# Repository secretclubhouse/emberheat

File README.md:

# EmberHeat

A Matter-enabled multi-zone thermostat system for hydronic heating, written in Rust for ESP32-C6. Controls heating zones via HomeKit, Google Home, and other Matter-compatible controllers.

## Architecture

**Cargo workspace** with three active crates:

| Crate | Purpose | Platform |
|-------|---------|----------|
| `emberheat-core` | Core control logic, traits, types | `no_std` compatible |
| `emberheat-matter` | Matter protocol types and cluster definitions | `no_std` compatible |
| `emberheat-esp32` | ESP32-C6 firmware (active) | ESP32-C6 bare-metal |
| `emberheat-linux` | Raspberry Pi implementation (preserved) | Linux |

### Core Library (`emberheat-core`)

Platform-agnostic library containing:
- **Temperature types** with Celsius/Fahrenheit conversion
- **Hysteresis control algorithm** (prevents relay chatter with ±0.5°C dead band)
- **Trait definitions** for sensors, GPIO, and state persistence
- **Sensor validation** (0°C - 37°C range)

### Matter Integration (`emberheat-matter`)

Smart home protocol support via [rs-matter](https://github.com/project-chip/rs-matter):
- **Thermostat Cluster** (0x0201) with heating and cooling support
- **Atomic state management** for cross-task zone state access
- **Zone-aware state** with target temperatures and system modes
- **Lock-free design** using portable-atomic for real-time safety
- **Dirty flag tracking** for efficient flash persistence

### ESP32 Implementation (`emberheat-esp32`)

Active firmware for ESP32-C6:
- **Embassy async runtime** for cooperative multitasking
- **Matter stack** with BLE + WiFi commissioning (single-radio and dual-radio modes)
- **Flash persistence** with wear-leveling via sequential-storage
- **Factory reset** via GPIO button (hold 5 seconds)
- **1-Wire temperature sensors** via RMT peripheral
- **BME280 I2C sensor** support
- **Relay control** via GPIO
- **WiFi connectivity** provisioned through Matter commissioning
- **MQTT logging** for monitoring
- **Matter bridge** connecting protocol state to control loops

### Linux Implementation (`emberheat-linux`)

Preserved but not actively developed. Uses:
- `rppal` for Raspberry Pi GPIO control
- 1-Wire via sysfs (`/sys/bus/w1/devices/`)
- HTTP fallback sensors via `reqwest`
- Redis for state persistence
- Prometheus for metrics export

## Quick Start (ESP32-C6)

### Prerequisites

```bash
# Install Rust (if needed)
curl --proto '=https' --tlsv1.2 -sSf https://sh.rustup.rs | sh

# Add ESP32 target
rustup target add riscv32imac-unknown-none-elf

# Install espflash
cargo install espflash
```

### Build and Flash

```bash
# Build with Matter support (single-radio: C6 WiFi + BLE time-shared)
make build-matter

# Build with dual-radio (C6 WiFi + H2 BLE over UART HCI)
make build-matter-dual-radio

# Flash Matter firmware and monitor serial output
make flash-monitor-matter

# Run tests (emberheat-core + emberheat-matter)
make test
```

### Matter Commissioning

After flashing, the device enters commissioning mode. Use the Apple Home app, Google Home, or any Matter controller to pair:

1. Power on the ESP32-C6
2. Open your Matter controller app
3. Scan the QR code or enter the setup code manually
4. The device appears as a Thermostat

Default commissioning credentials (configurable in `config.rs`):
- **Discriminator:** 3840
- **Passcode:** 20202021
- **Vendor ID:** 0xFFF1 (test)

The device supports up to 5 Matter fabrics simultaneously (HomeKit (2) + Google Home + Alexa + Home Assistant).

### Zone Configuration

Edit `emberheat-esp32/src/config.rs` to configure zones (1-16 supported):

```rust
pub const NUM_ZONES: usize = 7;

pub const ZONE_CONFIGS: [ZoneConfigData; NUM_ZONES] = [
    ZoneConfigData {
        name: "Living Room",
        relay_pin: 0,
        sensor_address: [0x28, ...],
        default_target_c: 21.1,
    },
    // ... more zones
];
```

Each zone appears as a separate thermostat endpoint in Matter controllers.

> **Note:** `NUM_ZONES` is currently set to 1 and `SENSOR_SOURCE` is `Mock` (set to `Mqtt` for remote MQTT sensors) for Matter commissioning testing. See `config.rs` for the full 7-zone configuration (commented out) and GPIO pin assignments.

## How It Works

### Control Loop (per zone)

```
┌─────────────┐     ┌──────────────┐     ┌─────────────┐
│ Read Sensor  │────▶│ Apply        │────▶│ Set Relay   │
│ Temperature  │     │ Hysteresis   │     │ State       │
└─────────────┘     └──────────────┘     └─────────────┘
       │                    │                     │
       ▼                    ▼                     ▼
  Validate 0-37°C    ±0.5°C dead band     GPIO HIGH/LOW
```

### Matter Integration

```
┌──────────────┐     ┌──────────────┐     ┌─────────────┐
│ Matter Stack │────▶│ Zone State   │────▶│ Control     │
│ (HomeKit etc)│     │ (Atomic)     │     │ Loop        │
└──────────────┘     └──────────────┘     └─────────────┘
  Set target temp    Lock-free R/W     Reads new target
  Set mode           Portable-atomic   Applies hysteresis
       │                    │
       ▼                    ▼
  BLE commission     Flash persist
  WiFi provision     (sequential-storage)
```

### Persistence

Zone setpoints and modes are persisted to flash with wear-leveling. On power loss, the device restores its last known configuration. Matter commissioning data (fabrics, network credentials) is also persisted.

### Safety

- Heating defaults to **OFF** on any error, except lost MQTT remote sensor readings, which run a bounded duty-cycle fallback (at most 6 hours, then OFF); see [docs/home-assistant-remote-sensors.md](docs/home-assistant-remote-sensors.md)
- Temperature readings validated before use
- State persisted to flash for power-loss recovery
- Hysteresis prevents rapid relay switching
- Factory reset available via GPIO 9 button (hold 5 seconds)

## Matter Clusters

The thermostat endpoint implements:

| Cluster | ID | Purpose |
|---------|-----|---------|
| Thermostat | 0x0201 | Temperature control, setpoints, system mode |
| Identify | 0x0003 | Device identification (HomeKit requirement) |
| Binding | 0x001E | External sensor support |
| Thermostat UI Config | 0x0204 | Temperature display format |
| Descriptor | 0x001D | Device type and cluster lists |

### Thermostat Attributes

| Attribute | Access | Description |
|-----------|--------|-------------|
| LocalTemperature | Read | Current temperature (0.01°C units) |
| OccupiedHeatingSetpoint | Read/Write | Heating target (7-30°C) |
| OccupiedCoolingSetpoint | Read/Write | Cooling target (10-35°C) |
| SystemMode | Read/Write | Off / Heat / Cool |
| ThermostatRunningState | Read | Currently heating/cooling/idle |
| ControlSequenceOfOperation | Read | CoolingAndHeating |

## Development

```bash
make dev        # Format + lint + test
make build      # Build core library
make test       # Run all tests
make lint       # Clippy lints
```

### Build Targets

```bash
# Core
make build              # Build emberheat-core
make build-esp32        # Build ESP32 firmware (MQTT mode, no Matter)

# Matter
make build-matter                    # Single radio (C6 WiFi + BLE)
make build-matter-dual-radio         # Dual radio (C6 WiFi + H2 BLE)
make flash-matter                    # Flash single radio
make flash-matter-dual-radio         # Flash dual radio
make flash-monitor-matter            # Flash + monitor
make flash-monitor-matter-dual-radio # Flash + monitor (dual radio)

# Quality
make test               # Run tests (core + matter)
make lint               # Clippy
make fmt                # Format
make dev                # Format + lint + test
```

## Project Status

- [x] Core hysteresis algorithm with tests
- [x] ESP32-C6 firmware with Embassy async runtime
- [x] 1-Wire and I2C sensor driver code (hardware testing pending — see [#1](https://github.com/secretclubhouse/emberheat/issues/1))
- [x] Multi-zone relay control (1-16 zones)
- [x] Matter commissioning (BLE + WiFi)
- [x] Thermostat cluster with heating and cooling
- [x] HomeKit / Google Home / Alexa integration via Matter
- [x] Atomic zone state management (lock-free)
- [x] Flash persistence with wear-leveling (fabrics + zone state)
- [x] Factory reset and zone state reset
- [x] Dual-radio support (ESP32-C6 WiFi + ESP32-H2 BLE)
- [x] MQTT telemetry in Matter mode
- [ ] Hardware sensor integration ([#1](https://github.com/secretclubhouse/emberheat/issues/1), [#2](https://github.com/secretclubhouse/emberheat/issues/2))
- [ ] Runtime zone configuration ([#5](https://github.com/secretclubhouse/emberheat/issues/5))
- [ ] Sensor auto-discovery ([#6](https://github.com/secretclubhouse/emberheat/issues/6))
- [ ] OTA firmware updates ([#7](https://github.com/secretclubhouse/emberheat/issues/7))

## License

Licensed under either of

- Apache License, Version 2.0 ([LICENSE-APACHE](LICENSE-APACHE) or <http://www.apache.org/licenses/LICENSE-2.0>)
- MIT License ([LICENSE-MIT](LICENSE-MIT) or <http://opensource.org/licenses/MIT>)

at your option.

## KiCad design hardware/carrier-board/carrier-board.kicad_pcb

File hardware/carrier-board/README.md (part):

# EmberHeat carrier board

A KiCad board, 168 x 114 mm, that holds an ESP32-C6-DevKitC-1 and an ESP32-H2-DevKitM-1 on sockets, switches seven zone circuits (24 V AC, one dry relay contact each) and takes its power from a USB-C supply. It mounts on a 35 mm DIN rail with two clips. Nothing on it connects to the 24 V AC except the relay contacts and the zone terminals.

**Status: designed and checked by software only; boards on order.** The owner ordered the board from OSH Park on 2026-11-16 and every part the same day, from Digi-Key and Newark (see [Ordering](#ordering)). No board has arrived and nothing has been assembled. The only parts test-fitted are the two dev boards, which the owner set on the printed template on 2026-11-16: both fit. No other part has been compared with its footprint. Distributor stock came from search snapshots, not live pages. The current in a zone circuit has not been measured. How far the back of the board sits from the metal rail is not established (see [Assembly](#assembly)). The [Known gaps](#known-gaps) section lists everything else. Read it before you order.

This board controls a heating system. It is a one-off built for one house, not a certified product. A mistake can leave a zone's valve open (heat on) or shut (no heat).

## Files

- `bom.csv`: one row per distinct part, with the exact KiCad symbol and footprint names.
- `part-checks.md`: datasheet figures that justify each part, and the drive arithmetic.
- `scripts/check_bom.py`: checks the bill of materials.
- `lib/`: dev board symbols and footprints, the DIN clip holes and the varistor footprint, written by `scripts/gen_lib.py` (`make lib`). `sym-lib-table` and `fp-lib-table` name it `emberheat`.
- `scripts/expected.py`: the pin lists and dimensions the checks compare the library against, written by hand.
- `scripts/check_lib.py`: checks the library, including that the sockets are not mirrored or reversed.
- `carrier-board.kicad_sch`: the schematic, written by `scripts/gen_schematic.py` (`make sch`, which also writes `build/netlist.xml`). Do not edit it by hand.
- `scripts/check_netlist.py`: checks the netlist against `expected.NETS`, the firmware's relay GPIOs and the datasheet pinouts.
- `scripts/check_erc.py` (and `make erc`): KiCad's electrical rules check, all severities; it must report 0 violations. No ERC exclusions are used.
- `make render`: writes `renders/schematic.png` (KiCad SVG export, cleaned by `scripts/svg_for_magick.py`, then ImageMagick).
- `carrier-board.kicad_pcb`: the board. `make board` (`scripts/gen_board.py`) places every part, draws the outline and silkscreen and routes the zone side (24 V AC, locked tracks); `make route` (`scripts/route.py`) routes the logic side and adds the ground pours, writing over the same file. Do not edit it by hand.
- `carrier-board.kicad_dru`: custom design rules: 3.0 mm between zone-side and logic-side copper; no logic-side track, via or pour in the zone strip (the rule area named `zone_strip`); tracks 0.5 mm from other-net through-hole pads; the dev boards' outlines on the silkscreen may meet the board edge.
- `routing/carrier-board.ses`: the Freerouting session `make route` replays, and `routing/carrier-board.dsn.sha256`, the router input it was made from.
- `make render-board`: writes `renders/board-*.png`: 3D views of both sides, each copper layer with its silkscreen as built (`*-layers.png`), and again without the ground pours so the tracks can be seen (`*-tracks.png`).
- `scripts/check_board.py`: checks the board against the netlist and the design, runs KiCad's design rule check, and checks `fab/`.
- `fab/`: what you send to the board house, and the print template. See [Fabrication files](#fabrication-files).
- `enclosure/` and `renders/enclosure-*.png`: the printable box (base, cover, dial strip, pane), generated by CadQuery scripts; the STEP and STL files are in `enclosure/out/`. See [Enclosure](#enclosure).
- `scripts/print_template.py`: makes the copy of the board that `fab/print-template.pdf` is plotted from.

## Ordering

Order from `bom.csv`, with these additions it does not list as rows (they are only in its notes). Check each against the manufacturer's part number on the distributor's page before paying.

**Parts ordered 2026-11-16 from Digi-Key:** everything in `digikey-cart.csv`, which is the order as placed (23 lines, all in stock, with spares). Two parts are not in that order: the relay (Digi-Key does not list 34.51.7.005.5010; it stocks the 34.51.7.005.0010, which has the same body, pins and coil but plain AgNi contacts without the gold layer) and the zone terminal plug 1757019 (out of stock at Digi-Key).

**Ordered 2026-11-16 from Newark:** 8 x relay 34.51.7.005.5010 (Newark 26M7138, $14.40 each; 7 plus a spare) and 7 x terminal plug 1757019 (Newark 71C4152, $2.06 each). One shipment from Newark's UK warehouse, quoted at 4-6 business days.

| What | Part | Qty | Note |
|---|---|---|---|
| Circuit board | `fab/carrier-board-gerbers.zip` | 1 board (or the house's minimum) | 2 layers, 1.6 mm, 168 x 114 mm. Smallest hole 0.4 mm (vias); smallest track and gap 0.25 mm. **Ordered 2026-11-16 from OSH Park** by uploading this zip; the owner looked at every layer in OSH Park's preview and all looked right. About $149, which matches their standard 2-layer service (three boards, 1.6 mm, 1 oz copper, ENIG finish, purple mask); the service name was not recorded. Chosen over JLCPCB (about $80 with shipping) to avoid import duties. The limits above were not checked against OSH Park's published rules beyond their accepting the files. Their boards arrive with small break-off nubs on the edges: file them flat before fitting the board in the enclosure. The parts had not been ordered or laid on the print template when the board was ordered. |
| Relay K1-K7 | Finder 34.51.7.005.5010 | 7 | 5 V coil (38.4 mA at 5 V, 130 ohm), AgNi + Au contacts, 6 A 250 V AC, minimum load 5 V / 2 mA. Flux-proof, not washable. |
| Zone terminal header J11-J17 | Phoenix 1757242 (MSTBA 2,5/2-G-5,08) | 7 | Soldered to the board. |
| **Zone terminal plug** | **Phoenix 1757019 (MSTB 2,5/2-ST-5,08)** | **7** | **Not a board part, so easy to forget. Without it nothing connects to the headers.** |
| Optocoupler U1-U7 | Lite-On LTV-817 | 7 | Any rank letter. |
| Transistor Q1-Q7 | onsemi 2N3904TF | 7 | The 2N3904 on tape with formed leads; Digi-Key lists the plain 2N3904 number as discontinued and names this as its replacement. Must be the EBC pinout (onsemi). Some makers sell CBE parts, which would be wrong. |
| Flyback diode D1-D7 | onsemi 1N4148 | 7 | |
| Varistor RV1-RV7 | Littelfuse V56ZA2P | 7 | 35 V AC, ZA "7mm" model: the coated disc is up to 9 mm across and 5 mm thick. Stands to the right of its relay. |
| Zone light D11-D17 / power light D8 | Kingbright WP710A10ID (red) / WP710A10GD (green) | 7 / 1 | 3 mm (T-1). Not the WP7113 parts, which are 5 mm. Cathode (flat side, shorter lead) in the square pad. |
| Resistors | Yageo CFR-25JB-52 series: 330 R x7, 1 k x15, 10 k x8, 5.1 k x2, 4.7 k x1 | 33 | Refs in `bom.csv`. |
| USB-C socket J1 | GCT USB4125-GF-A | 1 | The only surface-mount part. Power only. |
| 5 V screw terminal J2 | Phoenix 1729128 | 1 | |
| Fuse F1 | Bourns MF-RHT200-0 | 1 | 2.0 A hold, 3.8 A trip. |
| C1, C2 | Panasonic EEU-FR1A471 (470 uF), Kemet C317C104K5R5TA (100 nF) | 1 each | C1 is polarised: positive to +5 V. |
| Dev board sockets A1, A2 | Samtec SSW-116-01-T-S (C6), SSW-115-01-T-S (H2) | **2 of each (4 strips)** | One strip per side of each dev board. `bom.csv` lists one row each. |
| **JP1 shunt** | Samtec SNT-100-BK-T | **1** | Goes on the JP1 header (H2 3.3 V feed). Listed only in the note of the JP1 row. |
| JP1, J3 headers | Samtec TSW-102-07-T-S, TSW-103-07-T-S | 1 each | |
| DIN clips H5, H6 | Hammond 1427DINCLIP | **1 pack (2 clips + 4 screws)** | Digi-Key HM1489-ND. The #6 screws pass through 4.0 mm clearance holes in the board (bare board), or through the holes in the enclosure's base (see [Enclosure](#enclosure)). |
| Dev boards | ESP32-C6-DevKitC-1, ESP32-H2-DevKitM-1 | 1 each | You already have these. |
| DIN rail | 35 mm top-hat | | Not in `bom.csv`. |
| 5 V supply | USB-C, 5 V, rated 3 A | 1 | See Power. |

J4 (five spare pads for 3V3, GPIO20, TX, RX, GND) is **not fitted**: buy nothing for it. The four M3 corner holes take M3 screws if you want to fix the board by them; no screws are in `bom.csv`. Use washers no larger than 7 mm across (ISO 7089 M3): the copper keepout round each hole is sized for that.

## Power

Use a 5 V USB-C supply rated 3 A. A supply that offers only 0.5-0.9 A may not hold 5 V when several relays close. The worst case draw is an estimate of about 1 A at 5 V (not measured), so a weak supply could sag; if it does, the C6 can reset, which opens the relays. That would be safe but a nuisance.

- The 5 V input is the USB-C socket (J1, power only: no data lines) or the 2-way screw terminal J2 (labelled +5V and GND). Use one at a time.
- A resettable fuse F1 (2.0 A hold) follows the input.
- The 5 V rail feeds the relay coils, the zone lights and the C6 board's 5V pin. The C6 board makes the 3.3 V, which also feeds the H2 and the optocoupler LEDs.
- You can plug a computer into the C6 board's own USB port while the carrier is powered. Each USB port on the DevKitC-1 has a diode between it and the 5V pin (Espressif schematic V1.1; see `part-checks.md`), so the two 5 V sources do not feed each other.
- **With the wall supply absent, a computer on the C6 board's USB port powers the whole carrier** through that diode: the 5 V rail, the relay coils, the zone lights, and also J1 and J2 (the fuse passes current both ways), which then carry about 4.6 V. A computer port gives 0.5-0.9 A, so with several relays on it browns out and the C6 resets (relays open). For flashing that is fine; for running the zones use the wall supply.
- The 470 uF capacitor C1 charges at plug-in. A strict USB-C supply may see that as an overload and restart once (a single hiccup) before it settles; that is harmless.
- J2 has no reverse-polarity protection. Swapping its two wires puts -5 V on the rail, which will damage C1 (polarised) and the C6 dev board. Check the polarity against the `+5V` / `GND` labels before powering.
- The fuse (2.0 A hold, 3.8 A trip) is above what a 3 A USB-C supply will deliver, so with that supply it protects only against a fault fed from J2 by a larger supply; a short on the rail is limited by the USB-C supply itself.
- **The C6 dev board's own 3V3 jumper (J5 on the DevKitC-1) must be fitted**, as it is when the board ships. The carrier's 3.3 V rail comes from the C6's 3V3 header pin, which sits behind that jumper. With J5 removed the optocouplers and the H2 get no power.
- Nothing on the carrier uses, measures or shares the 24 V AC.

## The H2 jumper

JP1 is a 2-pin header with a shunt in the H2's 3.3 V feed. The board labels it `H2 3V3 — REMOVE BEFORE USING H2 USB`.

- Normal use: shunt fitted. The H2 runs from the C6 board's 3.3 V.
- **Before you plug a cable into the H2 board's own USB port (to flash it), remove the shunt.** Otherwise the two dev boards' 3.3 V regulators are connected together.

## Wiring

Each zone is a pair of wires closed by one relay contact (contacts 11 and 14, normally open; the normally closed contact 12 is not connected). The terminal plugs take 0.2-2.5 mm2 wire (18 AWG fits bare or in a 1.0 mm2 ferrule). The two wires of a pair are interchangeable. The relay is driven active-low: the C6 pin LOW closes the relay, as the firmware does.

| Zone | Terminal | Relay | Optocoupler | Transistor | Zone light | C6 GPIO | C6 dev board header pin (its J1 or J3, not the carrier's J1) |
|---|---|---|---|---|---|---|---|
| 1 | J11 (Z1) | K1 | U1 | Q1 | D11 | GPIO0 | J1 pin 7 |
| 2 | J12 (Z2) | K2 | U2 | Q2 | D12 | GPIO1 | J1 pin 8 |
| 3 | J13 (Z3) | K3 | U3 | Q3 | D13 | GPIO2 | J1 pin 12 |
| 4 | J14 (Z4) | K4 | U4 | Q4 | D14 | GPIO3 | J1 pin 13 |
| 5 | J15 (Z5) | K5 | U5 | Q5 | D15 | GPIO10 | J1 pin 10 |
| 6 | J16 (Z6) | K6 | U6 | Q6 | D16 | GPIO11 | J1 pin 11 |
| 7 | J17 (Z7) | K7 | U7 | Q7 | D17 | GPIO22 | J3 pin 6 |

The zone terminals run along the top edge, Z1 on the left. Each channel: C6 GPIO, 330 ohm, optocoupler LED, to 3.3 V. The optocoupler transistor drives the 2N3904 through 1 k (with 10 k to ground), the 2N3904 switches the relay coil, and the zone light (with 1 k) sits across the coil.

**The zone light shows that the relay is being driven, not that the contact has closed.** A stuck or burnt contact still lights it. To know a zone is closed, measure across its terminals.

The varistor across each contact passes about 10 uA of 24 V AC through an open contact (its capacitance; Littelfuse publishes no leakage figure; arithmetic in `part-checks.md`), far below what holds a valve or a control board's relay input on. A sensitive meter on AC volts may still show a voltage across an open, unloaded pair.

Other connections:

| C6 | H2 | Purpose |
|---|---|---|
| GPIO18 (10 k pull-up to 3.3 V) | GPIO0 | C6 transmit to H2 |
| GPIO19 | GPIO1 | H2 transmit to C6 |
| GPIO6 | GPIO2 | C6 ready-to-send |
| GPIO7 | GPIO3 | C6 clear-to-send |
| GPIO23 | RST | C6 resets the H2 |
| 3V3 (through JP1) | 3V3 | H2 power |
| GND | GND | Ground |

J3 is a 1-Wire sensor header (3V3, data on GPIO21, GND, 4.7 k pull-up). The current firmware does not use it. The C6 strapping pins (4, 5, 8, 9, 15), USB pins (12, 13), RST and both NC pins connect to nothing.

Enabling seven zones is a **firmware change**: `emberheat-esp32/src/config.rs` builds one zone (`NUM_ZONES = 1`) today with the seven-zone table commented out, and `test_relay_pins_are_valid_gpio` rejects GPIO22 until corrected. This board does not do that for you.

The zone circuit current has not been measured. The relays are rated 6 A, 250 V AC. If an AC current reading through one pair is above 2 A, revisit the relay choice before relying on the board (design decision, 2026-11-15).

## Assembly

This section is for the **bare board on DIN clips**. If you are printing the [enclosure](#enclosure), the clips go on the box instead and the board is screwed to the standoffs: follow the Enclosure section's assembly order, not step 7 below, and skip "Distance to the rail" (the box's floor is the insulation; see there). Do not do both.

**Warnings**

- Switch off the 24 V AC supply to the zone control board before touching zone wiring.
- The relays are flux-proof, not washable. Do not wash the board and do not use ultrasonic cleaning. Use a minimum of flux and wipe it locally if you must.
- The DIN clips fit one way only: **hook end up** (the back silkscreen marks the clip outline with `HOOK` at the hook end and `RAIL` where the rail runs). The other way round, a clip sits over solder joints.
- The back of the board has solder joints over both of the rail's flanges, among them every relay coil pin. See "Distance to the rail" below before you mount it.

Order, lowest parts first, so the board lies flat for each step (the heights of the parts were not checked, so use your judgement where parts are close in height):

1. USB-C socket J1 (surface mount, the only such part).
2. Diodes D1-D7 (banded end, the cathode, to +5 V) and all resistors.
3. 100 nF C2, varistors RV1-RV7, the fuse F1, headers JP1 and J3, transistors Q1-Q7, optocouplers U1-U7 (pin 1 is the LED anode side; see the schematic) and LEDs D8 and D11-D17. Check the polarity of every diode, LED, optocoupler and transistor against the schematic before soldering.
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
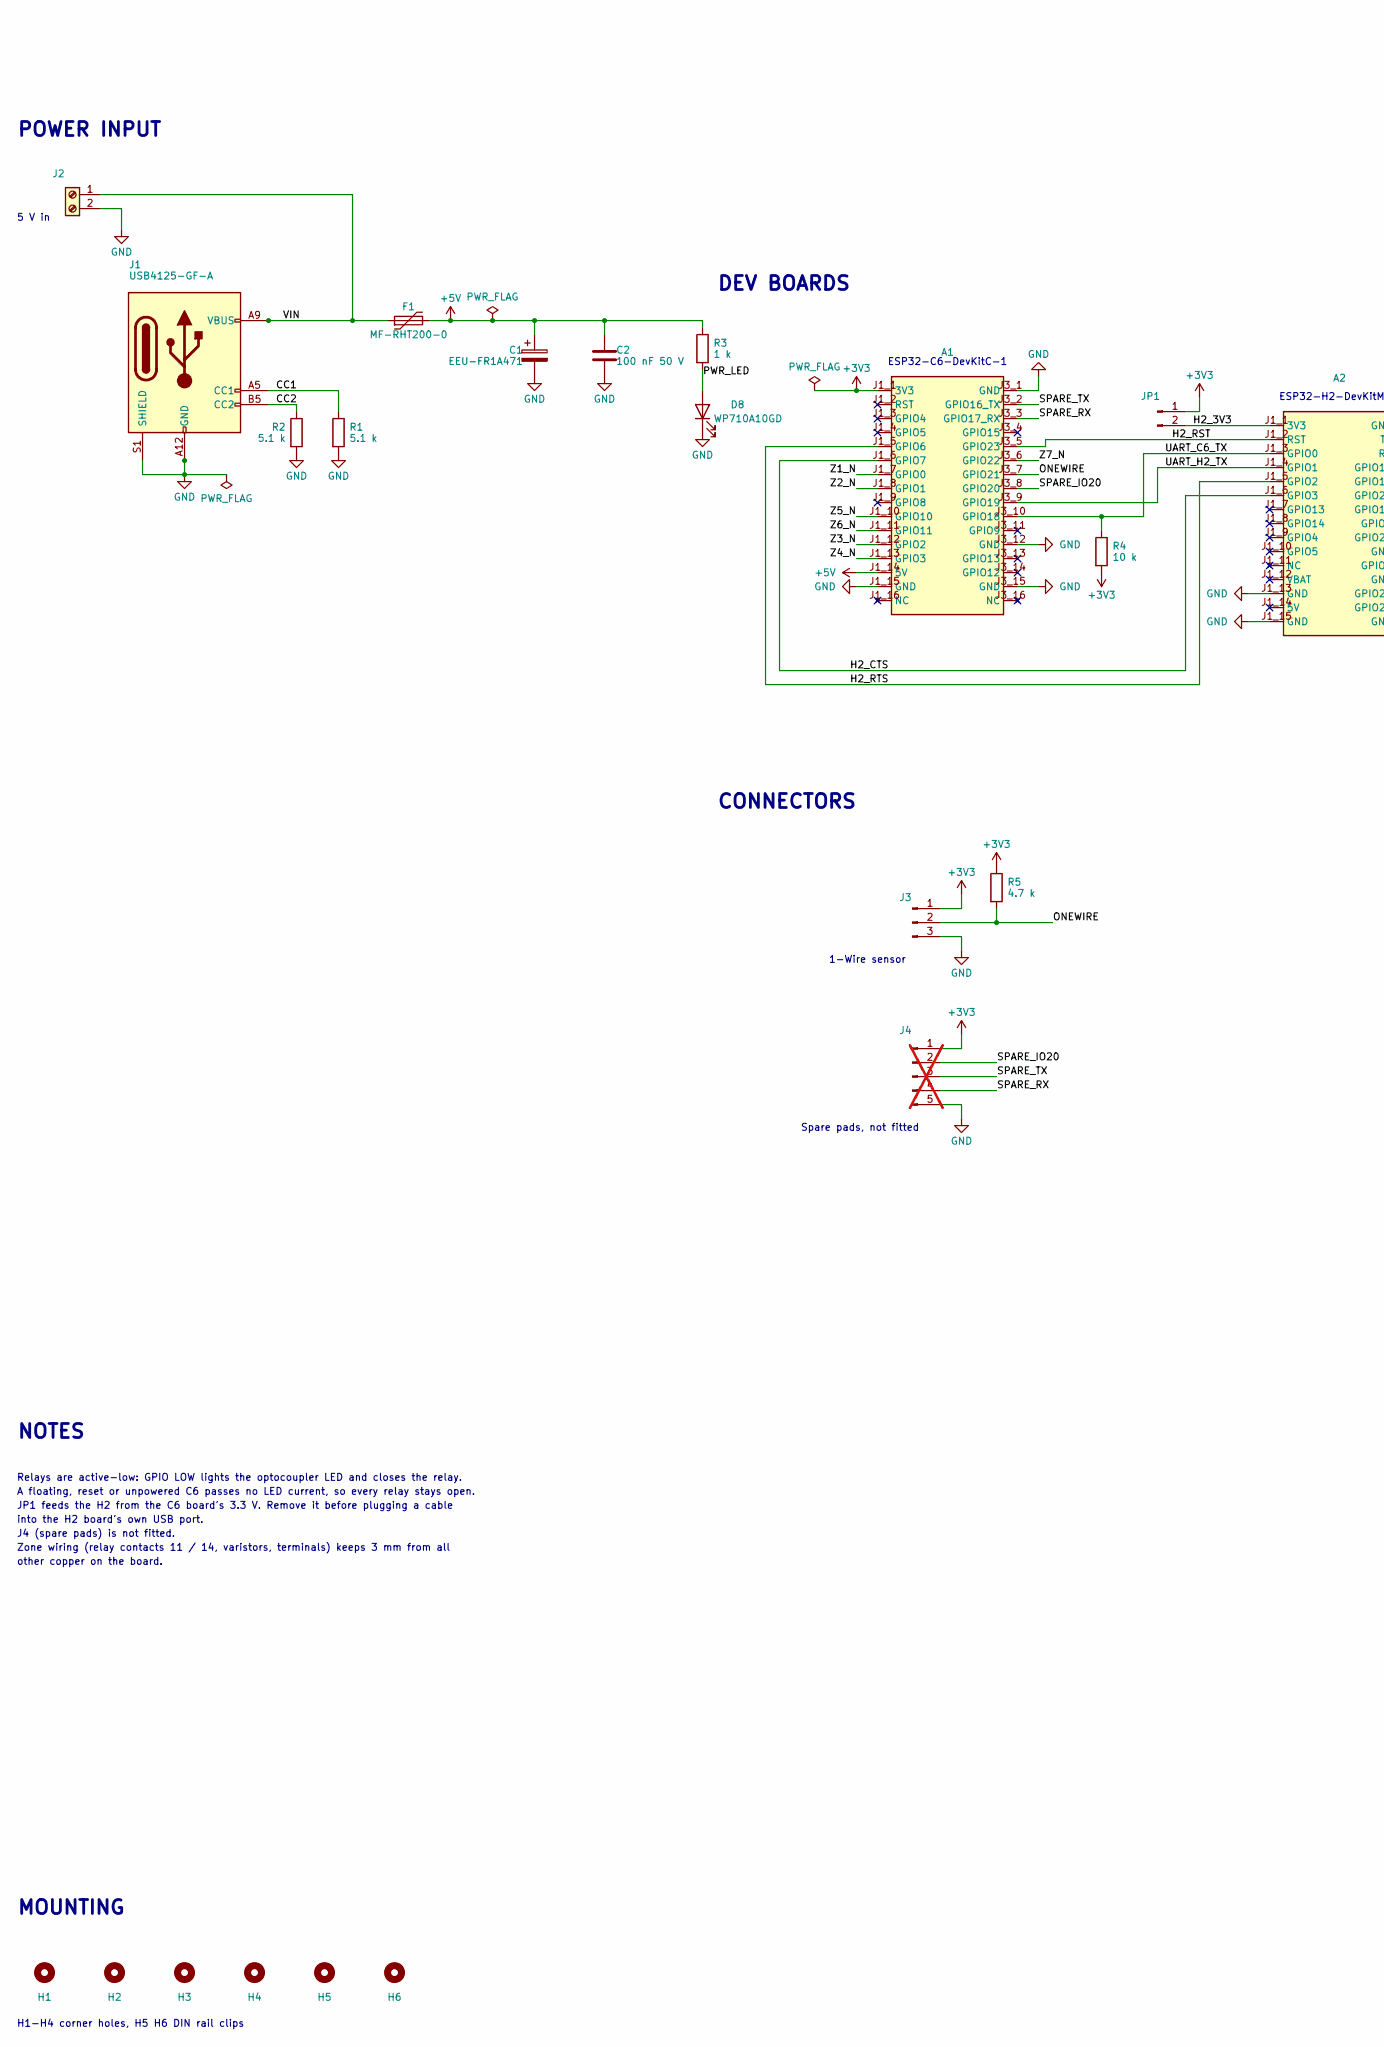
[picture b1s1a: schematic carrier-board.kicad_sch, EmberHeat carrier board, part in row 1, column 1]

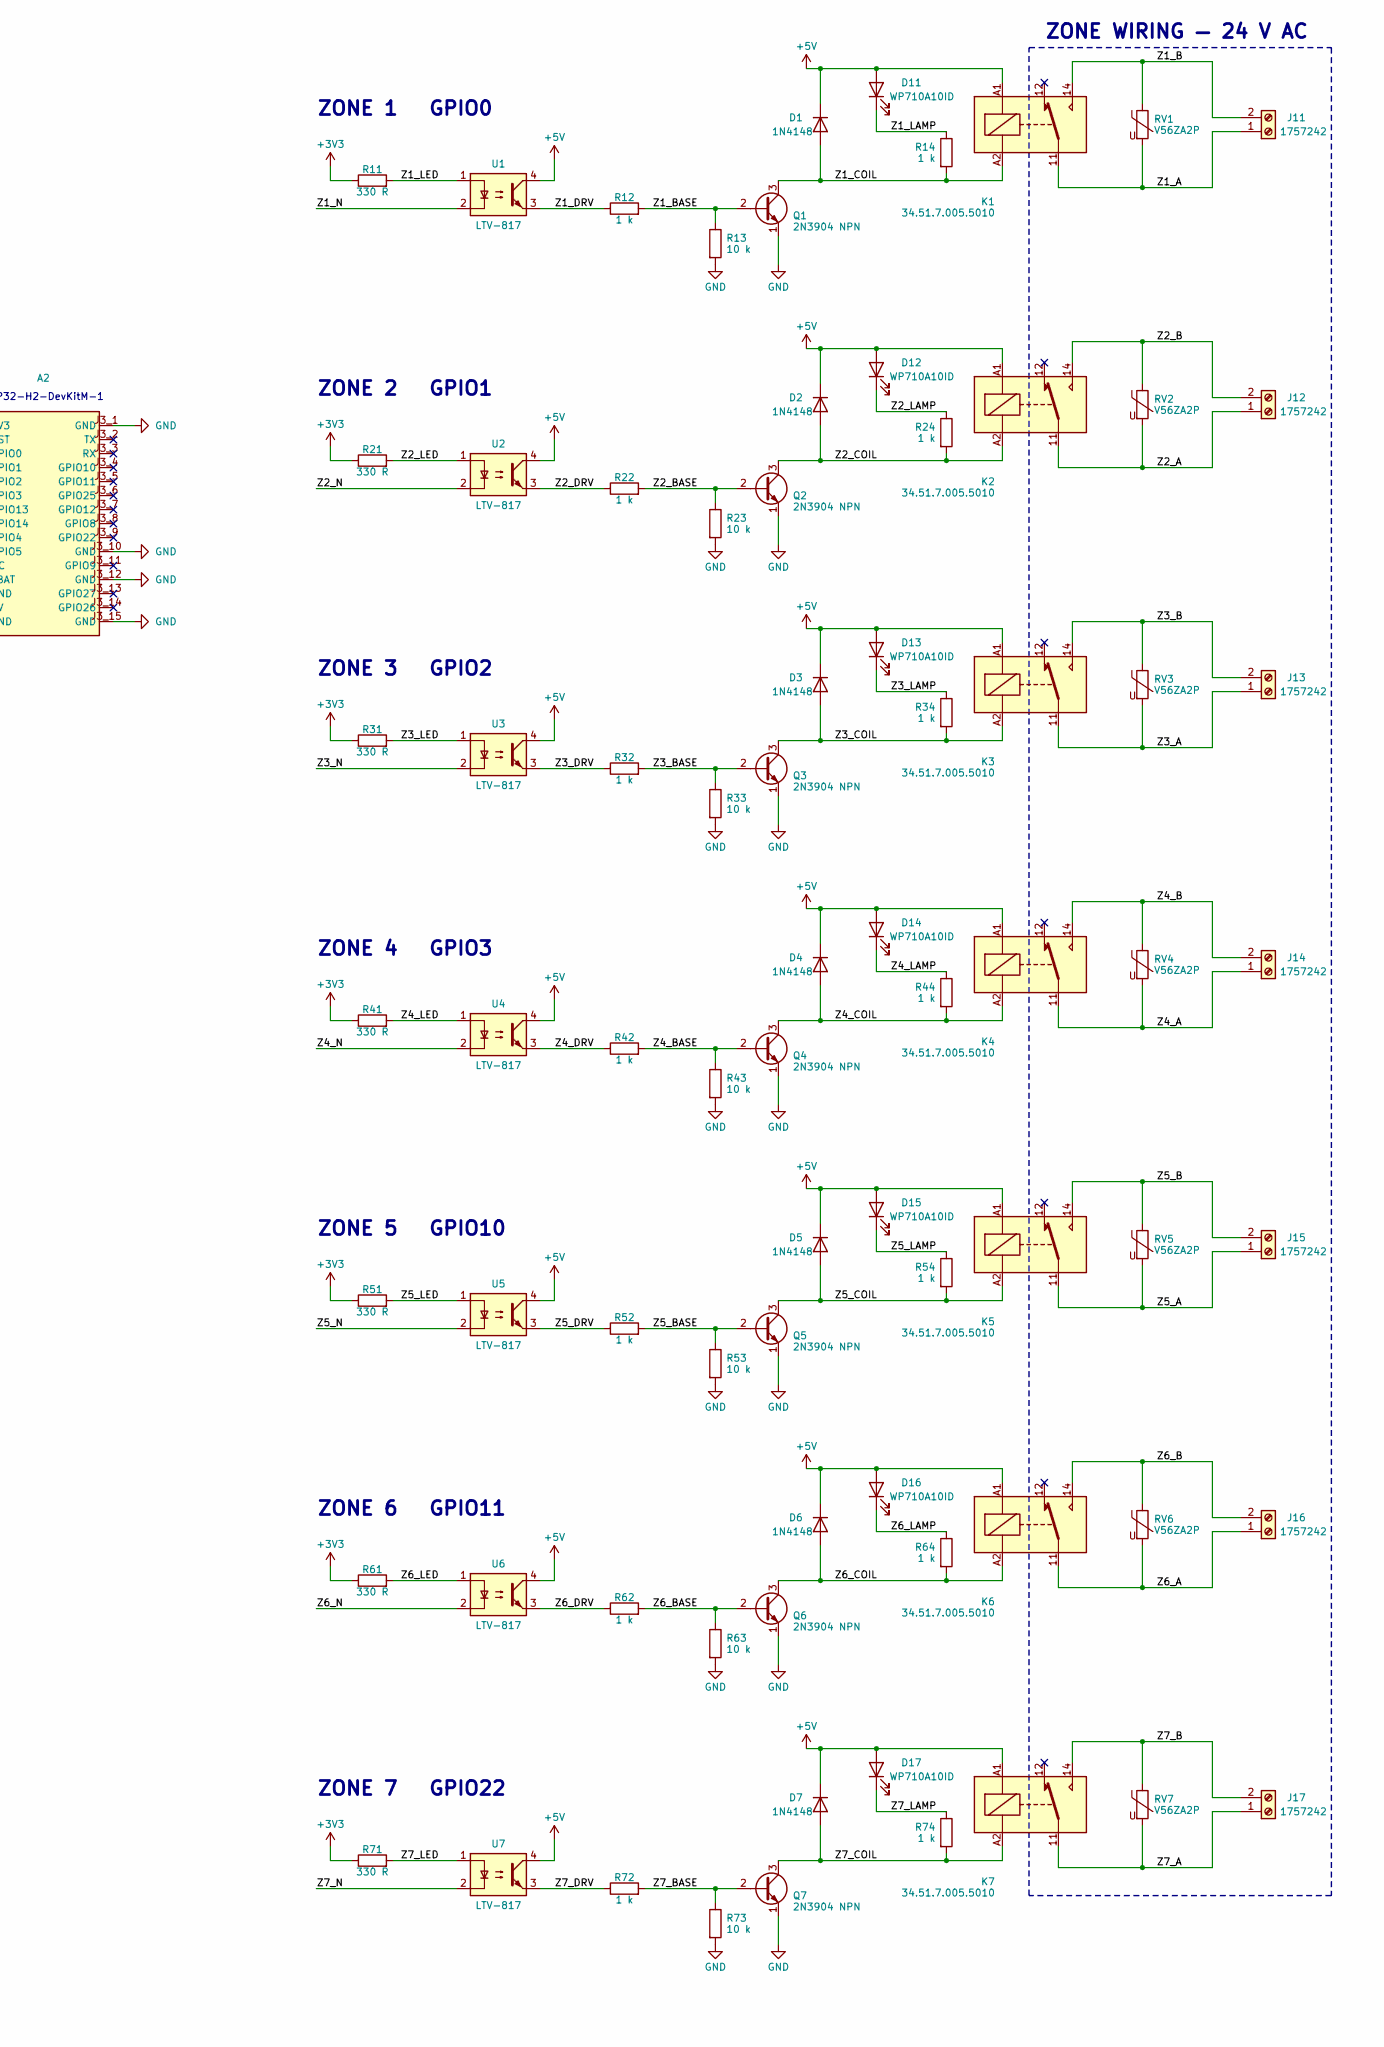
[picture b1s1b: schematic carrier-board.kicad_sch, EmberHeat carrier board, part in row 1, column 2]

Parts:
A1: 2x 16-way 2.54 mm female strip (C6 dev board); ESP32-C6-DevKitC-1; MPN SSW-116-01-T-S
A2: 2x 15-way 2.54 mm female strip (H2 dev board); ESP32-H2-DevKitM-1; MPN SSW-115-01-T-S
C1: 470 uF 10 V radial electrolytic; CP_Radial_D8.0mm_P3.50mm; MPN EEU-FR1A471
C2: 100 nF 50 V; C_Disc_D5.0mm_W2.5mm_P5.00mm; MPN C317C104K5R5TA
D1, D2, D3, D4, D5, D6, D7: 1N4148 flyback diode; D_DO-35_SOD27_P7.62mm_Horizontal; MPN 1N4148
D8: 3 mm (T-1) green LED, power light; LED_D3.0mm; MPN WP710A10GD
D11, D12, D13, D14, D15, D16, D17: 3 mm (T-1) red LED, zone light; LED_D3.0mm; MPN WP710A10ID
F1: Resettable fuse, hold 2.0 A, trip 3.8 A; Fuse_Bourns_MF-RHT200; MPN MF-RHT200-0
H1, H2, H3, H4: M3 corner hole, 3.2 mm; MountingHole_3.2mm_M3
H5, H6: DIN clip clearance holes for #6 screws (4.0 mm ho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; DIN_Clip; MPN 1427DINCLIP
J1: USB-C receptacle, power only, 6 pin; USB_C_Receptacle_GCT_USB4125-xx-x_6P_TopMnt_Horizontal; MPN USB4125-GF-A
J2: 5 V screw terminal 2-way 5.08 mm; TerminalBlock_Phoenix_MKDS-1,5-2-5.08_1x02_P5.08mm_Horizont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; MPN 1729128
J3: 3-pin header: 3V3, data, GND; PinHeader_1x03_P2.54mm_Vertical; MPN TSW-103-07-T-S
J4: 5 pads, unpopulated: 3V3, GPIO20, TX, RX, GND; PinHeader_1x05_P2.54mm_Vertical; not fitted
J11, J12, J13, J14, J15, J16, J17: Zone terminal header 2-way 5.08 mm; PhoenixContact_MSTBA_2,5_2-G-5,08_1x02_P5.08mm_Horizontal; MPN 1757242
JP1: 2-pin header and shunt, H2 3.3 V feed; PinHeader_1x02_P2.54mm_Vertical; MPN TSW-102-07-T-S
K1, K2, K3, K4, K5, K6, K7: 5 V coil, 1 NO contact, AgNi + Au; Relay_SPDT_Finder_34.51_Vertical; MPN 34.51.7.005.5010
Q1, Q2, Q3, Q4, Q5, Q6, Q7: 2N3904 NPN; TO-92_Inline_Wide; MPN 2N3904
R1, R2: 5.1 k; R_Axial_DIN0207_L6.3mm_D2.5mm_P10.16mm_Horizontal; MPN CFR-25JB-52-5K1
R3, R12, R14, R22, R24, R32, R34, R42, R44, R52, R54, R62, R64, R72, R74: 1 k; R_Axial_DIN0207_L6.3mm_D2.5mm_P10.16mm_Horizontal; MPN CFR-25JB-52-1K
R4, R13, R23, R33, R43, R53, R63, R73: 10 k; R_Axial_DIN0207_L6.3mm_D2.5mm_P10.16mm_Horizontal; MPN CFR-25JB-52-10K
R5: 4.7 k; R_Axial_DIN0207_L6.3mm_D2.5mm_P10.16mm_Horizontal; MPN CFR-25JB-52-4K7
R11, R21, R31, R41, R51, R61, R71: 330 R; R_Axial_DIN0207_L6.3mm_D2.5mm_P10.16mm_Horizontal; MPN CFR-25JB-52-330R
RV1, RV2, RV3, RV4, RV5, RV6, RV7: Varistor 35 V AC, ZA 7mm model (body up to 9 mm x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; Varistor_Littelfuse_ZA_7mm; MPN V56ZA2P
U1, U2, U3, U4, U5, U6, U7: Optocoupler DIP-4, CTR >= 50% at 5 mA; DIP-4_W7.62mm; MPN LTV-817

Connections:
+3V3: A1.J1_1 (3V3), J3.1, J4.1, JP1.1, R4.2, R5.1, R11.1, R21.1, R31.1, R41.1, R51.1, R61.1, R71.1
+5V: A1.J1_14 (5V), C1.1, C2.1, D1.1 (K), D2.1 (K), D3.1 (K), D4.1 (K), D5.1 (K), D6.1 (K), D7.1 (K), D11.2 (A), D12.2 (A), D13.2 (A), D14.2 (A), D15.2 (A), D16.2 (A), D17.2 (A), F1.2, K1.A1, K2.A1, K3.A1, K4.A1, K5.A1, K6.A1, K7.A1, R3.1, U1.4, U2.4, U3.4, U4.4, U5.4, U6.4, U7.4
/CC1: J1.A5 (CC1), R1.1
/CC2: J1.B5 (CC2), R2.1
/H2_3V3: A2.J1_1 (3V3), JP1.2
/H2_CTS: A1.J1_6 (GPIO7), A2.J1_6 (GPIO3)
/H2_RST: A1.J3_5 (GPIO23), A2.J1_2 (RST)
/H2_RTS: A1.J1_5 (GPIO6), A2.J1_5 (GPIO2)
/ONEWIRE: A1.J3_7 (GPIO21), J3.2, R5.2
/PWR_LED: D8.2 (A), R3.2
/SPARE_IO20: A1.J3_8 (GPIO20), J4.2
/SPARE_RX: A1.J3_3 (GPIO17_RX), J4.4
/SPARE_TX: A1.J3_2 (GPIO16_TX), J4.3
/UART_C6_TX: A1.J3_10 (GPIO18), A2.J1_3 (GPIO0), R4.1
/UART_H2_TX: A1.J3_9 (GPIO19), A2.J1_4 (GPIO1)
/VIN: F1.1, J1.A9 (VBUS), J1.B9 (VBUS), J2.1
/Z1_A: J11.1, K1.11, RV1.2
/Z1_B: J11.2, K1.14, RV1.1
/Z1_BASE: Q1.2 (B), R12.2, R13.1
/Z1_COIL: D1.2 (A), K1.A2, Q1.3 (C), R14.2
/Z1_DRV: R12.1, U1.3
/Z1_LAMP: D11.1 (K), R14.1
/Z1_LED: R11.2, U1.1
/Z1_N: A1.J1_7 (GPIO0), U1.2
/Z2_A: J12.1, K2.11, RV2.2
/Z2_B: J12.2, K2.14, RV2.1
/Z2_BASE: Q2.2 (B), R22.2, R23.1
/Z2_COIL: D2.2 (A), K2.A2, Q2.3 (C), R24.2
/Z2_DRV: R22.1, U2.3
/Z2_LAMP: D12.1 (K), R24.1
/Z2_LED: R21.2, U2.1
/Z2_N: A1.J1_8 (GPIO1), U2.2
/Z3_A: J13.1, K3.11, RV3.2
/Z3_B: J13.2, K3.14, RV3.1
/Z3_BASE: Q3.2 (B), R32.2, R33.1
/Z3_COIL: D3.2 (A), K3.A2, Q3.3 (C), R34.2
/Z3_DRV: R32.1, U3.3
/Z3_LAMP: D13.1 (K), R34.1
/Z3_LED: R31.2, U3.1
/Z3_N: A1.J1_12 (GPIO2), U3.2
/Z4_A: J14.1, K4.11, RV4.2
/Z4_B: J14.2, K4.14, RV4.1
/Z4_BASE: Q4.2 (B), R42.2, R43.1
/Z4_COIL: D4.2 (A), K4.A2, Q4.3 (C), R44.2
/Z4_DRV: R42.1, U4.3
/Z4_LAMP: D14.1 (K), R44.1
/Z4_LED: R41.2, U4.1
/Z4_N: A1.J1_13 (GPIO3), U4.2
/Z5_A: J15.1, K5.11, RV5.2
/Z5_B: J15.2, K5.14, RV5.1
/Z5_BASE: Q5.2 (B), R52.2, R53.1
/Z5_COIL: D5.2 (A), K5.A2, Q5.3 (C), R54.2
/Z5_DRV: R52.1, U5.3
/Z5_LAMP: D15.1 (K), R54.1
/Z5_LED: R51.2, U5.1
/Z5_N: A1.J1_10 (GPIO10), U5.2
/Z6_A: J16.1, K6.11, RV6.2
/Z6_B: J16.2, K6.14, RV6.1
/Z6_BASE: Q6.2 (B), R62.2, R63.1
/Z6_COIL: D6.2 (A), K6.A2, Q6.3 (C), R64.2
/Z6_DRV: R62.1, U6.3
/Z6_LAMP: D16.1 (K), R64.1
/Z6_LED: R61.2, U6.1
/Z6_N: A1.J1_11 (GPIO11), U6.2
/Z7_A: J17.1, K7.11, RV7.2
/Z7_B: J17.2, K7.14, RV7.1
/Z7_BASE: Q7.2 (B), R72.2, R73.1
/Z7_COIL: D7.2 (A), K7.A2, Q7.3 (C), R74.2
/Z7_DRV: R72.1, U7.3
/Z7_LAMP: D17.1 (K), R74.1
/Z7_LED: R71.2, U7.1
/Z7_N: A1.J3_6 (GPIO22), U7.2
GND: A1.J1_15 (GND), A1.J3_1 (GND), A1.J3_12 (GND), A1.J3_15 (GND), A2.J1_13 (GND), A2.J1_15 (GND), A2.J3_1 (GND), A2.J3_10 (GND), A2.J3_12 (GND), A2.J3_15 (GND), C1.2, C2.2, D8.1 (K), J1.A12 (GND), J1.B12 (GND), J1.S1 (SHIELD), J2.2, J3.3, J4.5, Q1.1 (E), Q2.1 (E), Q3.1 (E), Q4.1 (E), Q5.1 (E), Q6.1 (E), Q7.1 (E), R1.2, R2.2, R13.2, R23.2, R33.2, R43.2, R53.2, R63.2, R73.2

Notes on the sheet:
POWER INPUT
5 V in
DEV BOARDS
ESP32-C6-DevKitC-1
ESP32-H2-DevKitM-1
CONNECTORS
1-Wire sensor
Spare pads, not fitted
MOUNTING
H1-H4 corner holes, H5 H6 DIN rail clips
NOTES
Relays are active-low: GPIO LOW lights the optocoupler LED and closes the relay.
A floating, reset or unpowered C6 passes no LED current, so every relay stays open.
JP1 feeds the H2 from the C6 board's 3.3 V. Remove it before plugging a cable
into the H2 board's own USB port.
J4 (spare pads) is not fitted.
Zone wiring (relay contacts 11 / 14, varistors, terminals) keeps 3 mm from all
other copper on the board.
ZONE 1 GPIO0
ZONE 2 GPIO1
ZONE 3 GPIO2
ZONE 4 GPIO3
ZONE 5 GPIO10
ZONE 6 GPIO11
ZONE 7 GPIO22
ZONE WIRING — 24 V AC

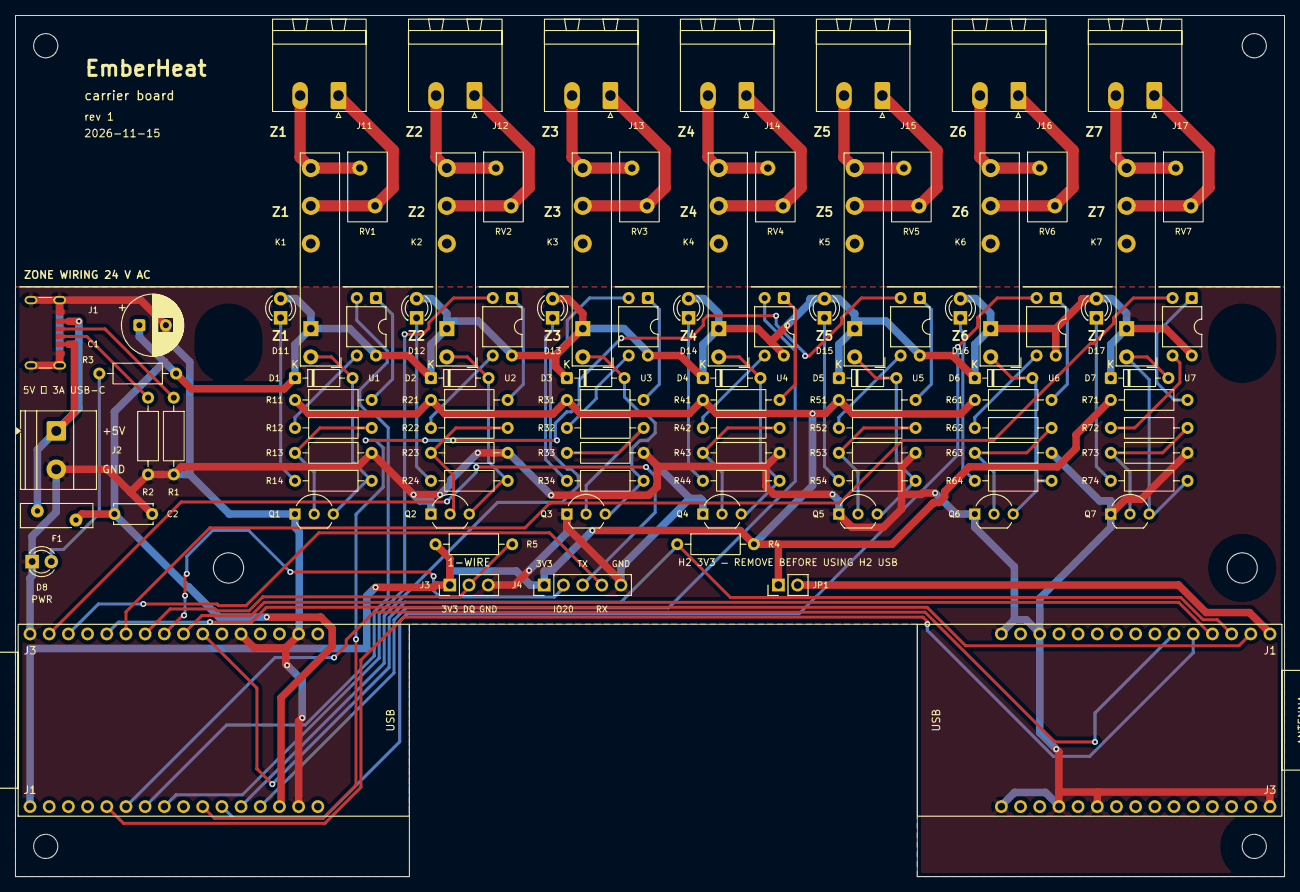
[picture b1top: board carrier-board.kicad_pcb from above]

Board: 2 copper layers, 168.0 x 114.0 mm, 99 parts (0 on the bottom side), 73 nets.

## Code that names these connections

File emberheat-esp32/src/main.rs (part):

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    // go wrong or block: network bring-up below can wait indefinitely.
    let relay1 = if NUM_ZONES >= 1 {
        Some(PIN_1.init(Esp32GpioPin::new(Output::new(
            peripherals.GPIO0,
            Level::High,
            OutputConfig::default(),
        ))))
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    };
    let relay2 = if NUM_ZONES >= 2 {
        Some(PIN_2.init(Esp32GpioPin::new(Output::new(
            peripherals.GPIO1,
            Level::High,
            OutputConfig::default(),
        ))))
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    };
    let relay3 = if NUM_ZONES >= 3 {
        Some(PIN_3.init(Esp32GpioPin::new(Output::new(
            peripherals.GPIO2,
            Level::High,
            OutputConfig::default(),
        ))))
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    };
    let relay4 = if NUM_ZONES >= 4 {
        Some(PIN_4.init(Esp32GpioPin::new(Output::new(
            peripherals.GPIO3,
            Level::High,
            OutputConfig::default(),
        ))))
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    };
    let relay5 = if NUM_ZONES >= 5 {
        Some(PIN_5.init(Esp32GpioPin::new(Output::new(
            peripherals.GPIO10,
            Level::High,
            OutputConfig::default(),
        ))))
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    };
    let relay6 = if NUM_ZONES >= 6 {
        Some(PIN_6.init(Esp32GpioPin::new(Output::new(
            peripherals.GPIO11,
            Level::High,
            OutputConfig::default(),
        ))))
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    };
    let relay7 = if NUM_ZONES >= 7 {
        Some(PIN_7.init(Esp32GpioPin::new(Output::new(
            peripherals.GPIO22,
            Level::High,
            OutputConfig::default(),
        ))))
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            });
        let uart = Uart::new(peripherals.UART1, uart_config)
            .expect("Failed to initialize HCI UART")
            .with_rx(peripherals.GPIO19) // RX (H2 TX -> C6 RX)
            .with_tx(peripherals.GPIO18) // TX (C6 TX -> H2 RX)
            .with_rts(peripherals.GPIO6) // RTS (C6 RTS -> H2 CTS)
            .with_cts(peripherals.GPIO7) // CTS (C6 CTS <- H2 RTS)
            .into_async();
        let (uart_rx, uart_tx) = uart.split();
        info!("HCI UART initialized");
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        // Open-drain: only ever pulls the line low; the H2 board's own pull-up
        // releases it, so the C6 never fights the H2's reset circuit.
        let mut h2_reset = Output::new(
            peripherals.GPIO23,
            Level::Low,
            OutputConfig::default().with_drive_mode(esp_hal::gpio::DriveMode::OpenDrain),
        );
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    // Only initialize zones where NUM_ZONES >= zone_number
    info!("Initializing {} zones...", NUM_ZONES);

    // Zone 1: GPIO0 (always initialized if NUM_ZONES >= 1)
    let (sensor1, pin1, state1) = if let Some(pin) = relay1 {
        info!("  Initializing Zone1 GPIO{}...", ZONE_CONFIGS[0].relay_pin);
        let sensor = SENSOR_1.init(ZoneSensor::for_zone(0));
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        (None, None, None)
    };

    // Zone 2: GPIO1
    let (sensor2, pin2, state2) = if let Some(pin) = relay2 {
        info!("  Initializing Zone2 GPIO{}...", ZONE_CONFIGS[1].relay_pin);
        let sensor = SENSOR_2.init(ZoneSensor::for_zone(1));
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        (None, None, None)
    };

    // Zone 3: GPIO2
    let (sensor3, pin3, state3) = if let Some(pin) = relay3 {
        info!("  Initializing Zone3 GPIO{}...", ZONE_CONFIGS[2].relay_pin);
        let sensor = SENSOR_3.init(ZoneSensor::for_zone(2));
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        (None, None, None)
    };

    // Zone 4: GPIO3
    let (sensor4, pin4, state4) = if let Some(pin) = relay4 {
        info!("  Initializing Zone4 GPIO{}...", ZONE_CONFIGS[3].relay_pin);
        let sensor = SENSOR_4.init(ZoneSensor::for_zone(3));
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        (None, None, None)
    };

    // Zone 5: GPIO10
    let (sensor5, pin5, state5) = if let Some(pin) = relay5 {
        info!("  Initializing Zone5 GPIO{}...", ZONE_CONFIGS[4].relay_pin);
        let sensor = SENSOR_5.init(ZoneSensor::for_zone(4));
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        (None, None, None)
    };

    // Zone 6: GPIO11
    let (sensor6, pin6, state6) = if let Some(pin) = relay6 {
        info!("  Initializing Zone6 GPIO{}...", ZONE_CONFIGS[5].relay_pin);
        let sensor = SENSOR_6.init(ZoneSensor::for_zone(5));
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        (None, None, None)
    };

    // Zone 7: GPIO22
    let (sensor7, pin7, state7) = if let Some(pin) = relay7 {
        info!("  Initializing Zone7 GPIO{}...", ZONE_CONFIGS[6].relay_pin);
        let sensor = SENSOR_7.init(ZoneSensor::for_zone(6));
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
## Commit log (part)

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2025-10-24 Update documentation
2025-10-25 Fix bad import
2025-10-27 Update gh actions to only use linux
2025-10-27 Fix test to not require redis connection
2025-10-27 Document and implement configuration file search locations
2025-10-27 Refactor test assertion formatting in Config module
2025-11-05 matter ffi (Rust): Modernize documentation style in FFI modules and build script
2025-11-05 Remove unused import: error from tracing in Matter FFI wrapper
2025-11-05 Remove unnecessary blank line in FFI mod.rs header
2025-11-05 Add comprehensive unit tests for Matter FFI bindings and wrapper modules
2025-11-05 build: Add platform detection and support for pre-built Matter libraries in build script
2025-11-05 Migrate Matter library integration from git submodule to download-based workflow
2025-11-05 Fix Matter archive extraction to use correct directory structure
2025-11-05 scripts: Switch Matter download from tarball to git clone, initialize submodules
2025-11-06 chore: Update .dockerignore to exclude build artifacts, logs, and third-party source
2025-11-06 ci: Improve Matter build logging and platform detection in build.rs
2025-11-06 ci: Split formatting and linting checks into separate job and update workflow dependencies
2025-11-06 Refactor usage of Path and PathBuf and improve idiomatic Rust usage in build.rs
2025-11-06 Fix safety issues in Matter bidirectional callbacks
    This commit addresses two critical safety issues in the callback
    implementation identified during code review:
    1. Fix unaligned memory access in C++ callback (CVE potential)
    - Problem: Used reinterpret_cast<int16_t*>(value) which could cause
    crashes on architectures with strict alignment requirements (ARM, SPARC)
    - Solution: Use std::memcpy() to safely copy bytes into properly aligned
2025-11-06 Add safety checks for single-device limitation in global callback architecture
    This commit addresses a critical architectural limitation where the global
    g_matter_device variable could cause callbacks to be routed to the wrong
    device if multiple Matter devices were created.
    Problem:
    - g_matter_device is a global variable used by callbacks
    - emberAfPostAttributeChangeCallback has a fixed signature (Matter framework)
2025-11-07 Add comprehensive thread safety to Matter C++ FFI layer
    This commit resolves three critical race conditions in the Matter FFI:
    1. Device initialization race condition:
    - Added mutex-protected check-and-set in matter_device_init
    - Prevents two threads from both passing null check and creating multiple devices
    - Uses std::lock_guard for RAII safety
    2. Shutdown race condition:
2025-11-07 Add Grafana dashboards and datasource configuration
    - Create grafana/datasources/prometheus.yml for Prometheus datasource
    - Create grafana/dashboards/dashboard.yml for dashboard provisioning
    - Create comprehensive thermostat.json dashboard with 8 panels:
    * Current temperature time series per zone
    * Target temperature time series per zone
    * Heat status state timeline
2025-11-10 Add comprehensive AI agent documentation
    Create two documentation files to help AI assistants work with the codebase:
    - .claude/CLAUDE.md: Claude-specific instructions covering project
    architecture, testing strategy, code patterns, safety considerations,
    and development workflows. Includes quick reference for constants,
    ports, and important file locations.
    - AGENTS.md: Comprehensive AI agent guidelines with architecture diagrams,
2025-11-12 Comment out Docker image build job in release workflow
2025-11-17 fix: Add Ember AF compatibility shims and update Matter wrapper for new SDK API and correct QR code format
2025-11-17 feat: Auto-generate ZAP data in Docker builds and commit to repo
    This commit updates the Docker build process to automatically generate
    ZAP configuration files from matter/thermostat.zap and makes them
    committable to the repository.
    Changes:
    - scripts/docker-build-matter-internal.sh: Add Step 5.5 to generate ZAP
    data from /output/matter/thermostat.zap if present. Prioritize
2025-11-17 Add ZAP-generated files from matter/thermostat.zap
2025-12-23 Remove project-chip/connectedhomeip. Will be switching back to projectchip/rs-matter
2025-12-29 feat: add ESP32-C6 bare-metal implementation
    Create thermos-esp32 crate for ESP32-C6 RISC-V microcontroller:
    Architecture:
    - Uses thermos-core for control logic
    - Pure Embassy async runtime (no Tokio)
    - esp-hal 1.0 for hardware access
    - esp-rtos 0.2 for Embassy integration
2025-12-29 docs: add project status and migration documentation
    Add comprehensive status documentation:
    MATTER_INTEGRATION.md:
    - Matter integration removal notes
    - Guidance for re-adding Matter support
    - ZAP file generation instructions
    ESP32_STATUS.md:
2025-12-29 feat: add MQTT client for ESP32 with rust-mqtt
    - Implement async MQTT client using rust-mqtt v0.3
    - Temperature readings published every 6 seconds
    - State change events for heating on/off
    - Device status messages
    - Auto-reconnection with exponential backoff
    - Channel-based async message queuing (QoS 0)
2025-12-29 test: add comprehensive test suite for ESP32
    Add 63 tests for MQTT and WiFi functionality:
    MQTT tests (mqtt_tests.rs - 20 tests):
    - Configuration validation (broker, port, device_id)
    - Topic formatting and size limits
    - JSON payload generation and formatting
    - Temperature conversion accuracy
2026-01-27 docs: add ESP32 Matter thermostat design document
    Comprehensive design for completing the thermos-rust project:
    - 7-zone heating thermostat on single ESP32-C6
    - Matter integration via rs-matter-embassy for HomeKit/Google/Alexa
    - MQTT state reporting for monitoring
    - Hardware parts list
    - 5-phase implementation plan including future Thread support
2026-01-27 feat(esp32): add multi-sensor manager for shared 1-Wire bus
    Add sensors.rs module with:
    - SharedOneWireBus: Thread-safe wrapper for shared 1-Wire bus access
    - SharedDs18b20Sensor: Individual sensor wrapper referencing shared bus
    - MockSensor: Testing sensor with configurable temperature
    Also includes:
    - Make esp-hal-rmt-onewire optional (onewire-rmt feature) due to
2026-01-27 feat(esp32): add sensor scan utility for discovering DS18B20 addresses
2026-01-27 fix: correct 1-Wire search algorithm for 3+ devices
    The search algorithm was not properly tracking discrepancy points when
    backtracking. When following the previous 0-path at a discrepancy point
    BEFORE the current backtrack position, we must still record it as a
    potential new backtrack point for subsequent iterations.
    Bug: With sensors A, B, C where A differs from B,C at bit 9, and B differs
    from C at bit 8, the search would find A and B but miss C because after
2026-01-27 chore: ignore .claude/settings.local.json
2026-01-27 fix: resolve CI build errors on Linux
    - Replace From trait impls with helper functions for RelayState/Level
    conversion to avoid orphan rule violation (E0117)
    - Fix unused variable warning in hal/linux.rs
2026-01-27 refactor: focus build/test on thermos-core, deprioritize thermos-linux
    - Set default-members in workspace to thermos-core and thermos-esp32
    - Simplify Makefile for ESP32-focused development
    - Update CI workflow to only build/test thermos-core
    - Update pre-commit hook to only check thermos-core
    - Remove unused Docker files (Dockerfile, Dockerfile.armv7, docker-compose.yml)
    thermos-linux is preserved in the workspace but not actively developed.
2026-01-27 Remove unused folder
2026-01-28 feat(matter): import thermostat cluster and create ThermostatHooks trait
    - Use rs_matter::import!(Thermostat) for IDL-based cluster definition
    - Create HEATING_ONLY_CLUSTER with restricted feature set (heating only)
    - Define ThermostatHooks trait following OnOffHooks pattern
    - Add OutOfBandMessage enum for async notifications
    - Re-export generated types: SystemModeEnum, RelayStateBitmap, etc.
    - Implement ThermostatHooks for references (&T)
2026-01-28 docs: add Task 7.5 to extract thermos-matter crate
    - Task 7.5: Extract Matter module to separate crate for host testing
    - Enables no_std by default with optional std feature
    - Task 8 now depends on Task 7.5 completion
    - Detailed steps for crate extraction and import updates
2026-01-28 fix(ci): add checks:write permission for security audit
    The rustsec/audit-check action needs permission to create GitHub
    Check Runs for PR annotations.
2026-01-28 feat(esp32): conditional zone initialization based on NUM_ZONES
    - Only initialize GPIO, sensors, and state for configured zones
    - Only spawn tasks for zones where NUM_ZONES >= zone_number
    - Reduces memory usage when running fewer than 7 zones
2026-01-28 feat: increase MAX_ZONES from 7 to 16, document real constraints
    - MAX_ZONES increased to 16 in thermos-matter and thermos-esp32
    - Document that adding zones beyond 7 requires adding task functions in main.rs
    - Document GPIO and memory constraints (~15-20 pins, ~1-2KB per zone)
    - Update tests to use new MAX_ZONES value
2026-01-28 feat: add .env.example and auto-load .env.local in Makefile
    - Create .env.example with WiFi and MQTT configuration template
    - Update Makefile to auto-load .env.local or .env if present
    - Add environment documentation to make help
    - Update setup target to mention .env.local
2026-01-28 docs: add Phase 3 Matter integration design
    Phase 3 covers rs-matter-embassy integration:
    - Dependencies: sysgrok forks with Embassy 0.5+ compatibility
    - Architecture: Matter stack as Embassy task sharing ZoneThermostatState
    - Handler approach: thin wrapper (Option B) with documented refactor path
    - Phased implementation: 1 zone → 3 zones → configurable N zones
    - Validation checklist and risk mitigation
2026-01-28 feat(matter): implement Handler trait for ZoneThermostatCluster
    Implement rs-matter's Handler trait with read/write methods:
    Read support for:
    - LocalTemperature (nullable i16)
    - OccupiedHeatingSetpoint (i16)
    - MinHeatSetpointLimit (i16, read-only)
    - MaxHeatSetpointLimit (i16, read-only)
2026-01-29 feat(matter): add bt-hci dependency for external BLE controller
2026-01-29 feat(matter): add dual-radio initialization in main
2026-01-29 feat(matter): enable hardware flow control for HCI UART
2026-01-29 fix(matter): sync initial temperature before Matter task starts
    This ensures HomeKit sees valid LocalTemperature during commissioning,
    preventing it from caching 'not supported' status due to NULL temperature.
    The initial mock temperature (20.0C) is synced to Matter state for all
    zones before spawning the Matter task, for both single-radio and
    dual-radio configurations.
2026-02-18 docs: fix stale references after rename and restructure
    Update documentation to reflect current project structure:
    - ARCHITECTURE.md: update persistence (NVS flash vs Redis), mark
    completed items, update startup times, fix Embassy/Tokio section
    - TESTING.md: fix mock paths from root src/ to emberheat-linux/src/
    - .devcontainer/README.md: remove C++ Matter wrapper references,
    update to reflect rs-matter pure Rust approach
2026-02-18 ci: speed up security audit by using pre-built cargo-audit binary
    Replace rustsec/audit-check@v2 (compiles from source, ~6min) with
    taiki-e/install-action (downloads pre-built binary, ~seconds).
